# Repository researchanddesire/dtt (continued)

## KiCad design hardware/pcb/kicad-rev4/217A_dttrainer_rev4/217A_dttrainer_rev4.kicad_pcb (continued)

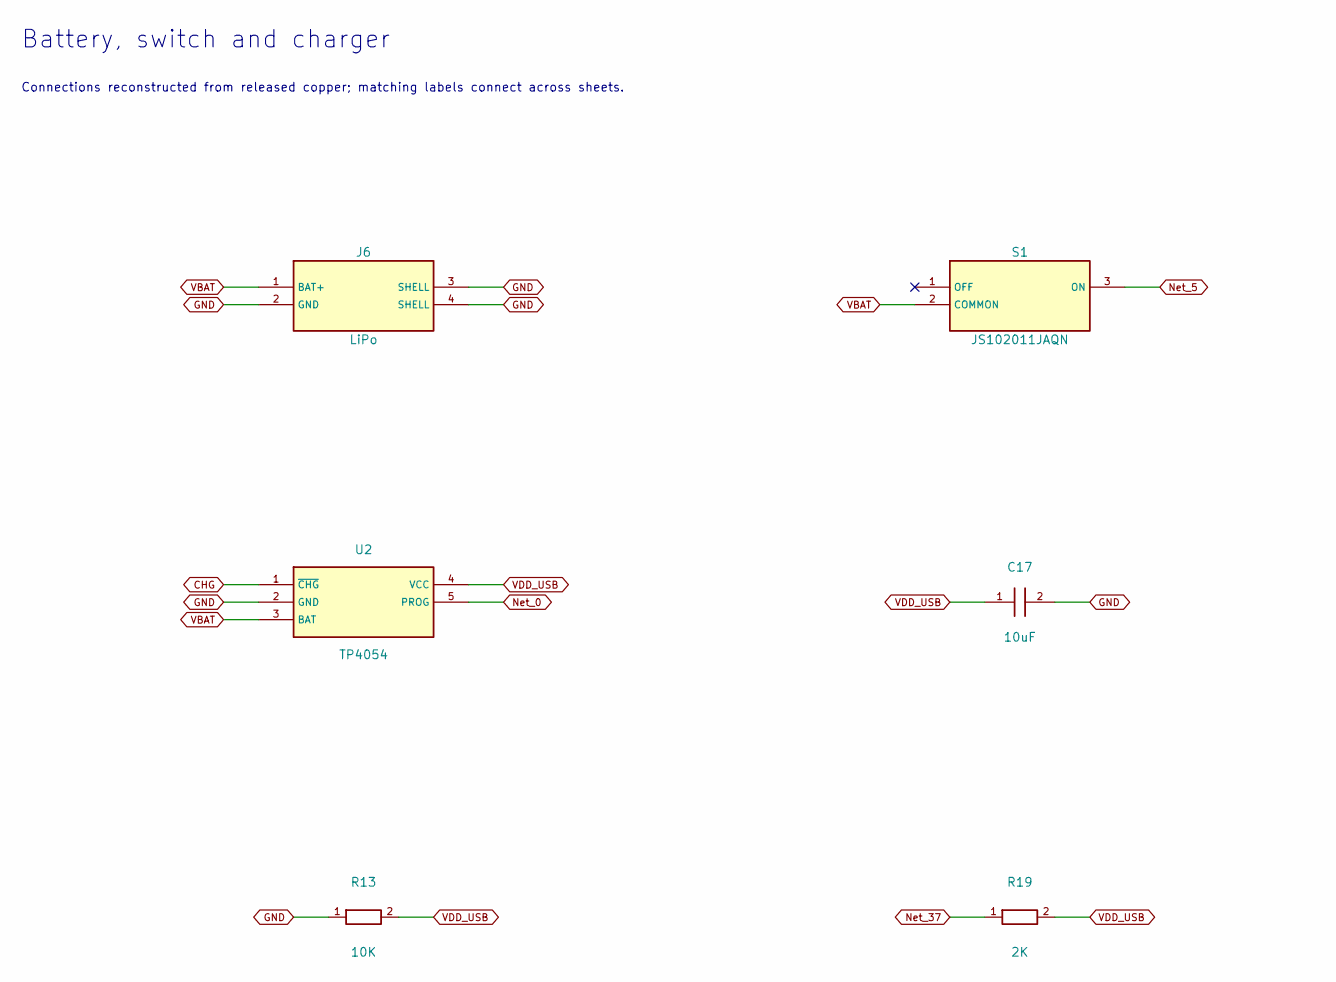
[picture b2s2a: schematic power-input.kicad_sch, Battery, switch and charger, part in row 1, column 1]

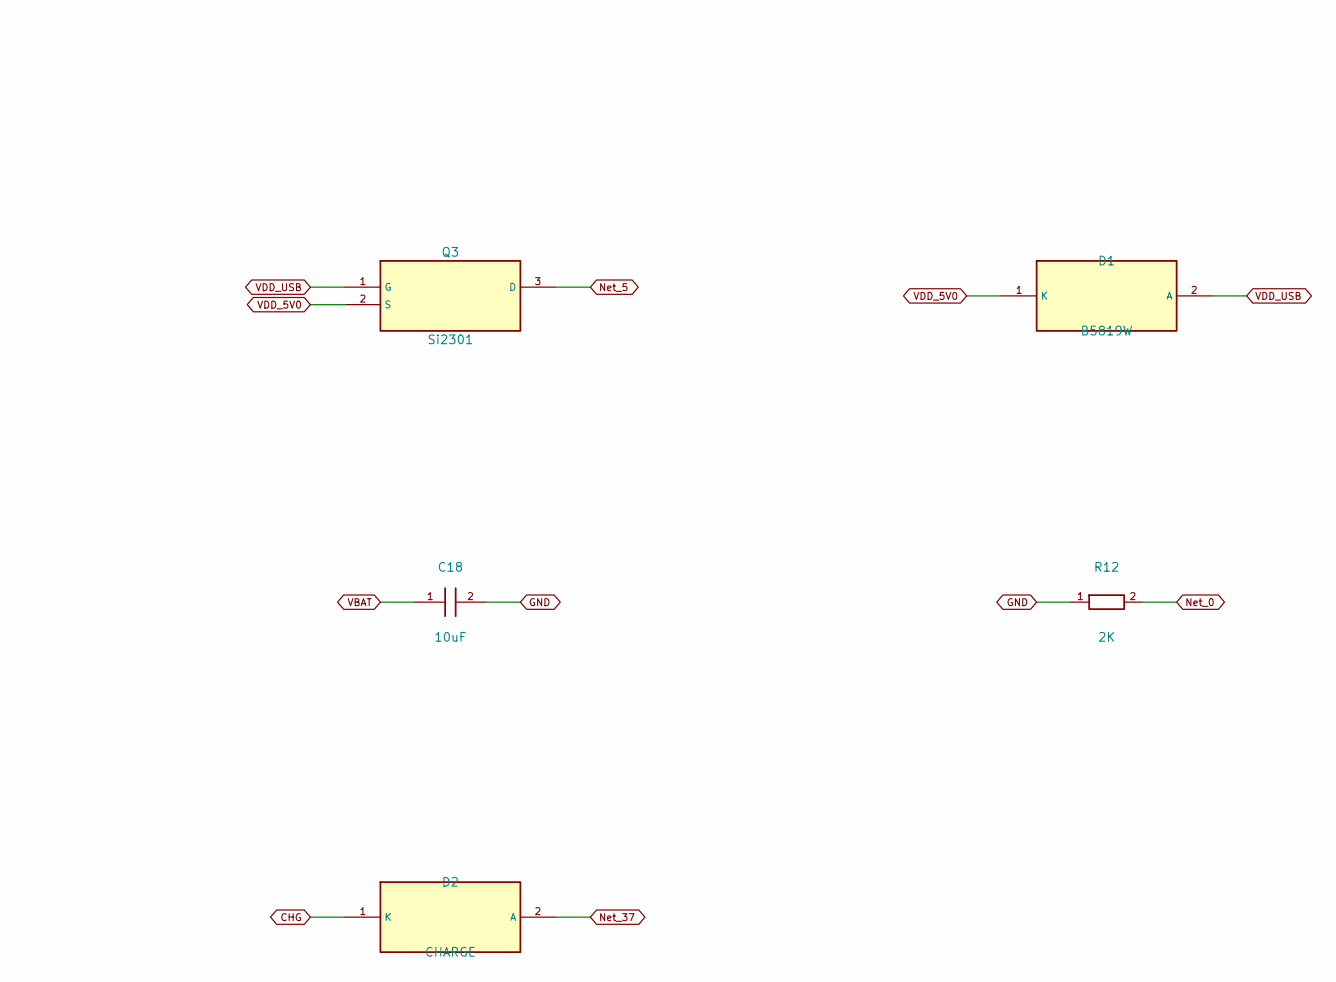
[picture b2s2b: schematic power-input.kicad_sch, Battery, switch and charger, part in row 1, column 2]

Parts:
C17: 10uF; C17; LCSC C89827
C18: 10uF; C18; LCSC C89827
D1: B5819W; D1; LCSC C22463588
D2: CHARGE; D2; LCSC C94868
J6: LiPo; J6; LCSC C2763702
Q3: Si2301; Q3; LCSC C727151
R12: 2K; R12; LCSC C105581
R13: 10K; R13; LCSC C99198
R19: 2K; R19; LCSC C105581
S1: JS102011JAQN; S1; LCSC C221658
U2: TP4054; U2; LCSC C32574

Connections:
CHG: D2.1 (K), U2.1 (~CHG); also elsewhere on the board
GND: C17.2, C18.2, J6.2 (GND), J6.3 (SHELL), J6.4 (SHELL), R12.1, R13.1, U2.2 (GND); also elsewhere on the board
Net_0: R12.2, U2.5 (PROG)
Net_5: Q3.3 (D), S1.3 (ON)
Net_37: D2.2 (A), R19.1
VBAT: C18.1, J6.1 (BAT+), S1.2 (COMMON), U2.3 (BAT); also elsewhere on the board
VDD_5V0: D1.1 (K), Q3.2 (S); also elsewhere on the board
VDD_USB: C17.1, D1.2 (A), Q3.1 (G), R13.2, R19.2, U2.4 (VCC); also elsewhere on the board

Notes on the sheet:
Battery, switch and charger
Connections reconstructed from released copper; matching labels connect across sheets.

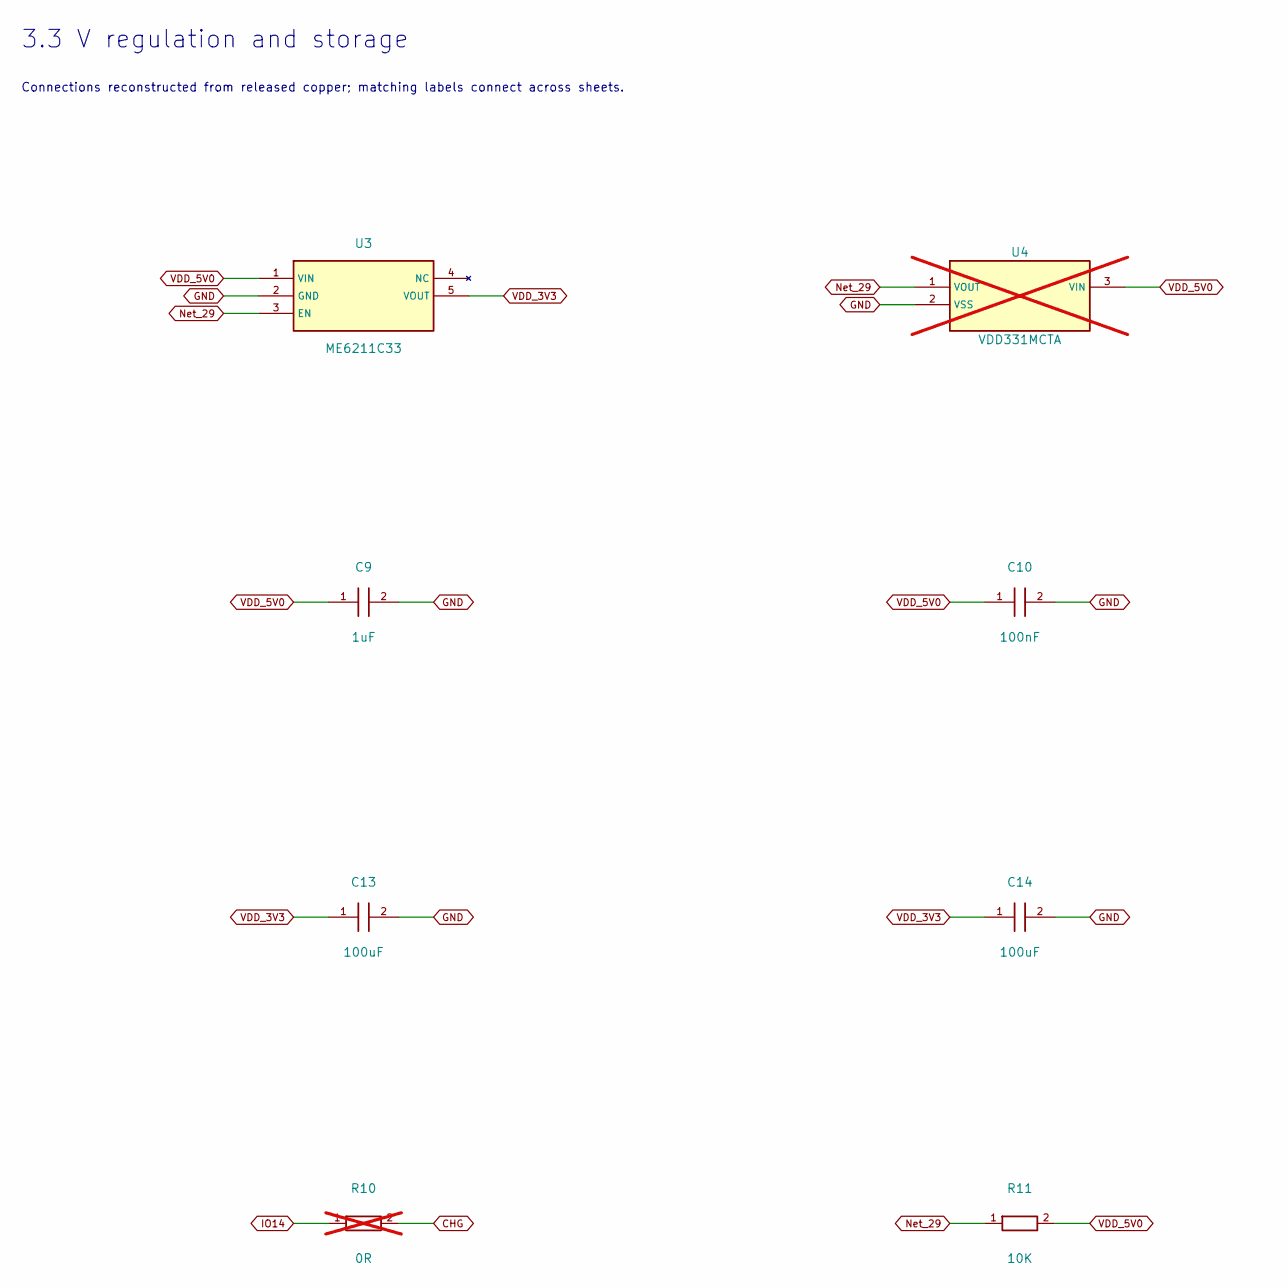
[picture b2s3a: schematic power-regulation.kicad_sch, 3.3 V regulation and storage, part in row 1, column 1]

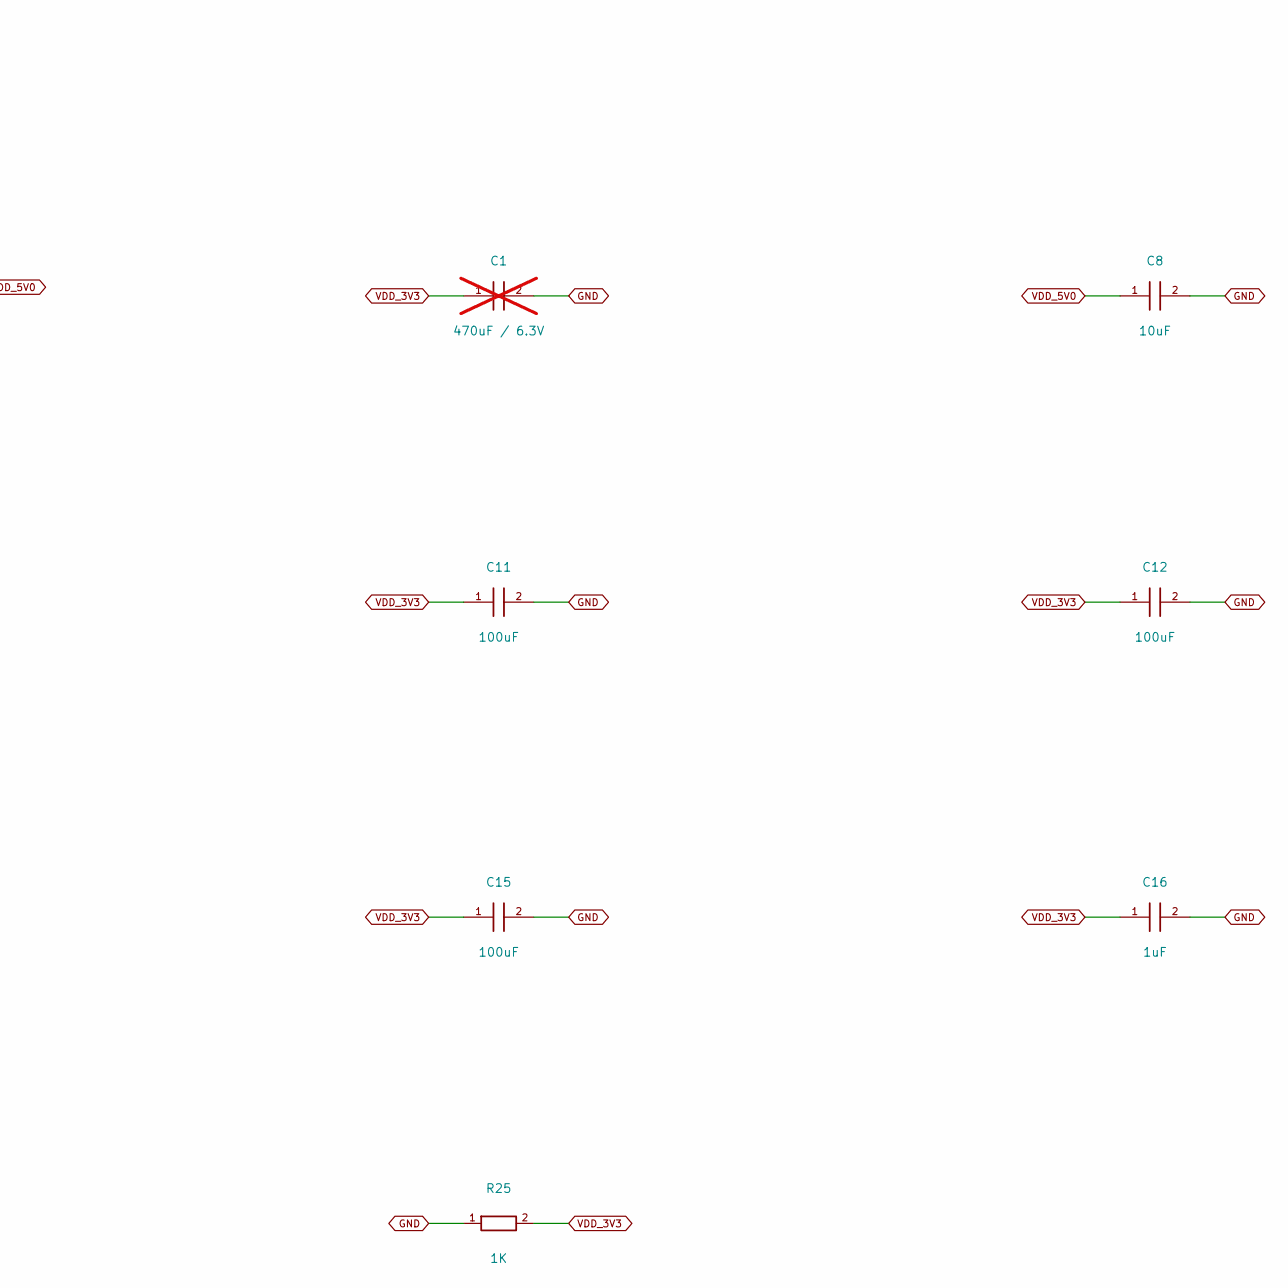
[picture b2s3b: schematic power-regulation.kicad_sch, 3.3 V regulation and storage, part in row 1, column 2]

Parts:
C1: 470uF / 6.3V; C1; LCSC DNP; not fitted
C8: 10uF; C8; LCSC C89827
C9: 1uF; C9; LCSC C106248
C10: 100nF; C10; LCSC C108079
C11: 100uF; C11; LCSC C15008
C12: 100uF; C12; LCSC C15008
C13: 100uF; C13; LCSC C15008
C14: 100uF; C14; LCSC C15008
C15: 100uF; C15; LCSC C15008
C16: 1uF; C16; LCSC C106248
R10: 0R; R10; LCSC DNP; not fitted
R11: 10K; R11; LCSC C99198
R25: 1K; R25; LCSC C14676
U3: ME6211C33; U3; LCSC C82942
U4: VDD331MCTA; U4; LCSC DNP; not fitted

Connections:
CHG: R10.2; also elsewhere on the board
GND: C1.2, C8.2, C9.2, C10.2, C11.2, C12.2, C13.2, C14.2, C15.2, C16.2, R25.1, U3.2 (GND), U4.2 (VSS); also elsewhere on the board
IO14: R10.1; also elsewhere on the board
Net_29: R11.1, U3.3 (EN), U4.1 (VOUT)
VDD_3V3: C1.1, C11.1, C12.1, C13.1, C14.1, C15.1, C16.1, R25.2, U3.5 (VOUT); also elsewhere on the board
VDD_5V0: C8.1, C9.1, C10.1, R11.2, U3.1 (VIN), U4.3 (VIN); also elsewhere on the board

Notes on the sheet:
3.3 V regulation and storage
Connections reconstructed from released copper; matching labels connect across sheets.

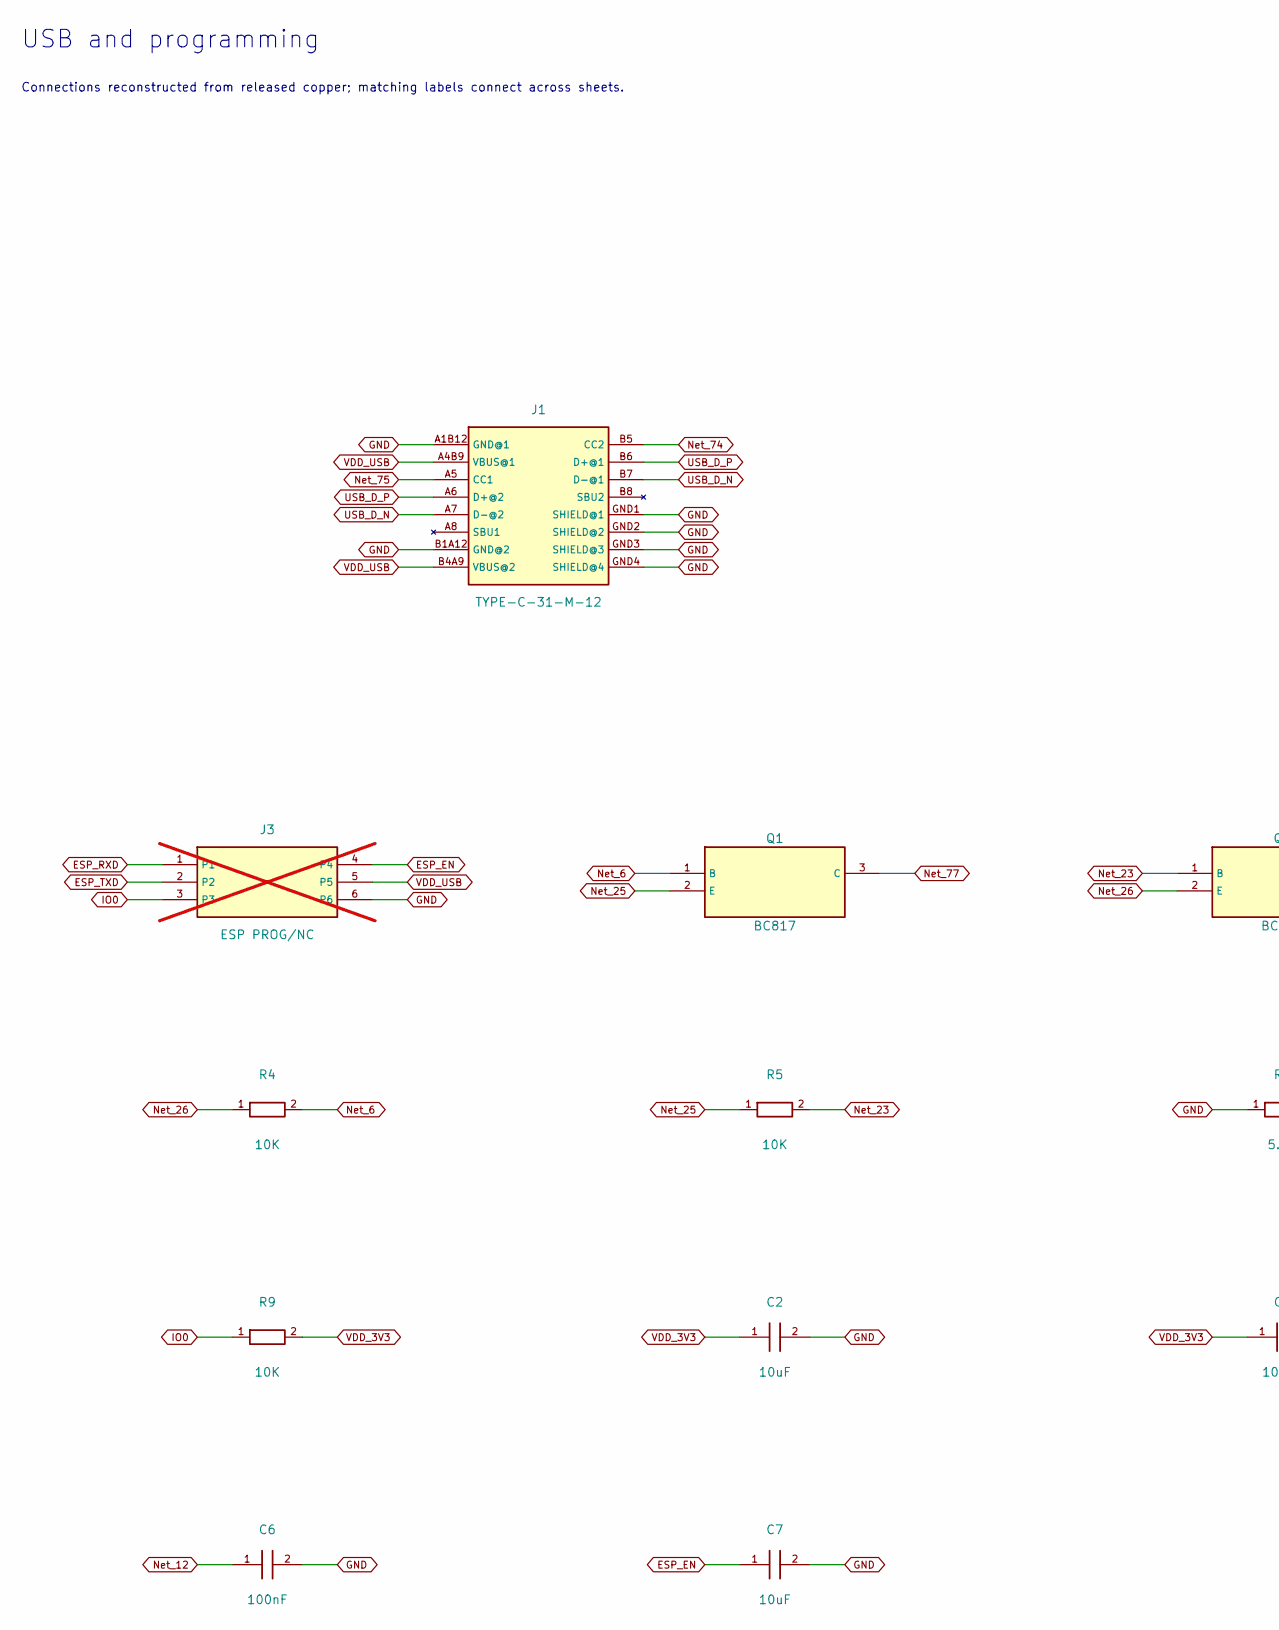
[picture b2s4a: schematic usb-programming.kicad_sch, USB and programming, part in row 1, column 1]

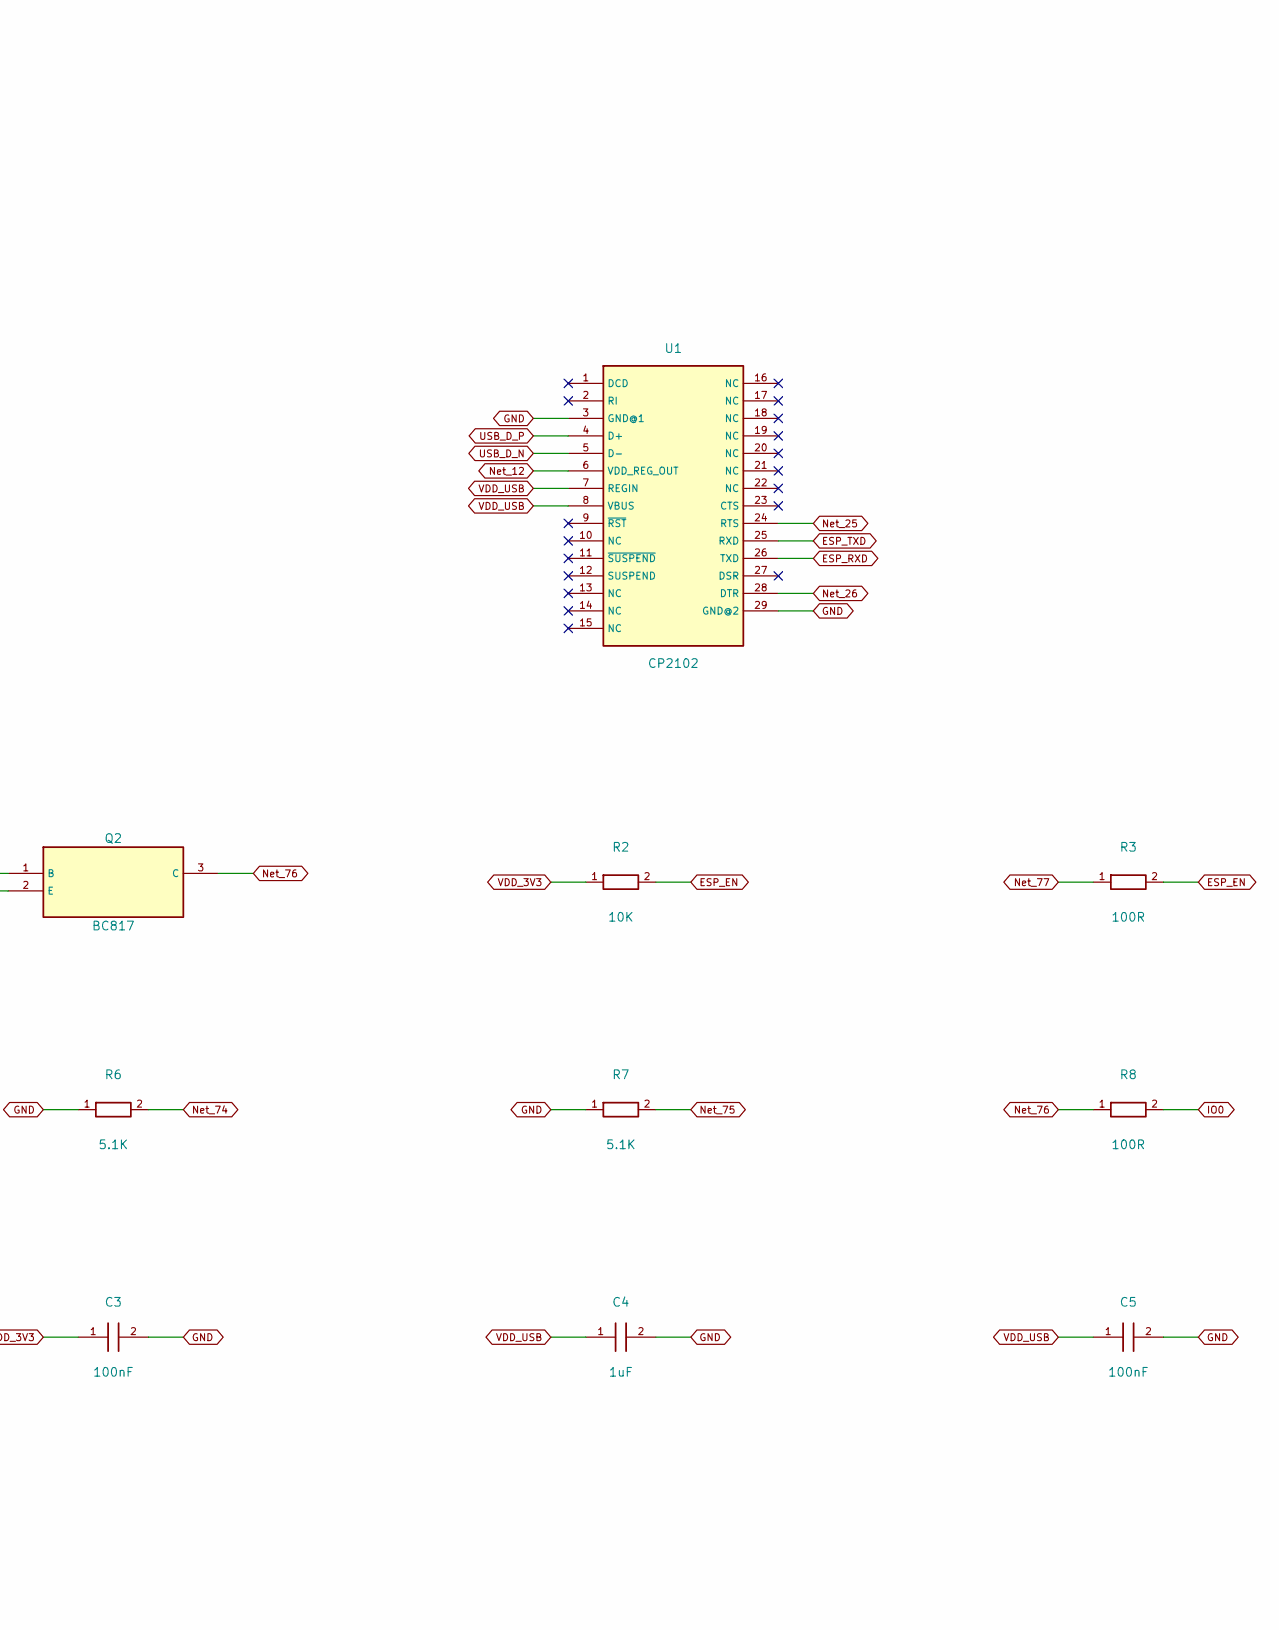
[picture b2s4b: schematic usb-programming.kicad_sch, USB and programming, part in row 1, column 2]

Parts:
C2: 10uF; C2; LCSC C237435
C3: 100nF; C3; LCSC C519438
C4: 1uF; C4; LCSC C106248
C5: 100nF; C5; LCSC C108079
C6: 100nF; C6; LCSC C108079
C7: 10uF; C7; LCSC C109457
J1: TYPE-C-31-M-12; J1; LCSC C165948
J3: ESP PROG/NC; J3; LCSC DNP; not fitted
Q1: BC817; Q1; LCSC C8658
Q2: BC817; Q2; LCSC C8658
R2: 10K; R2; LCSC C99198
R3: 100R; R3; LCSC C110091
R4: 10K; R4; LCSC C99198
R5: 10K; R5; LCSC C99198
R6: 5.1K; R6; LCSC C105580
R7: 5.1K; R7; LCSC C105580
R8: 100R; R8; LCSC C110091
R9: 10K; R9; LCSC C99198
U1: CP2102; U1; LCSC C6568

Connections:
ESP_EN: C7.1, J3.4, R2.2, R3.2; also elsewhere on the board
ESP_RXD: J3.1, U1.26 (TXD); also elsewhere on the board
ESP_TXD: J3.2, U1.25 (RXD); also elsewhere on the board
GND: C2.2, C3.2, C4.2, C5.2, C6.2, C7.2, J1.A1B12 (GND@1), J1.B1A12 (GND@2), J1.GND1 (SHIELD@1), J1.GND2 (SHIELD@2), J1.GND3 (SHIELD@3), J1.GND4 (SHIELD@4), J3.6, R6.1, R7.1, U1.3 (GND@1), U1.29 (GND@2); also elsewhere on the board
IO0: J3.3, R8.2, R9.1; also elsewhere on the board
Net_6: Q1.1 (B), R4.2
Net_12: C6.1, U1.6 (VDD_REG_OUT)
Net_23: Q2.1 (B), R5.2
Net_25: Q1.2 (E), R5.1, U1.24 (RTS)
Net_26: Q2.2 (E), R4.1, U1.28 (DTR)
Net_74: J1.B5 (CC2), R6.2
Net_75: J1.A5 (CC1), R7.2
Net_76: Q2.3 (C), R8.1
Net_77: Q1.3 (C), R3.1
USB_D_N: J1.A7 (D-@2), J1.B7 (D-@1), U1.5 (D-)
USB_D_P: J1.A6 (D+@2), J1.B6 (D+@1), U1.4 (D+)
VDD_3V3: C2.1, C3.1, R2.1, R9.2; also elsewhere on the board
VDD_USB: C4.1, C5.1, J1.A4B9 (VBUS@1), J1.B4A9 (VBUS@2), J3.5, U1.7 (REGIN), U1.8 (VBUS); also elsewhere on the board

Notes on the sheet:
USB and programming
Connections reconstructed from released copper; matching labels connect across sheets.

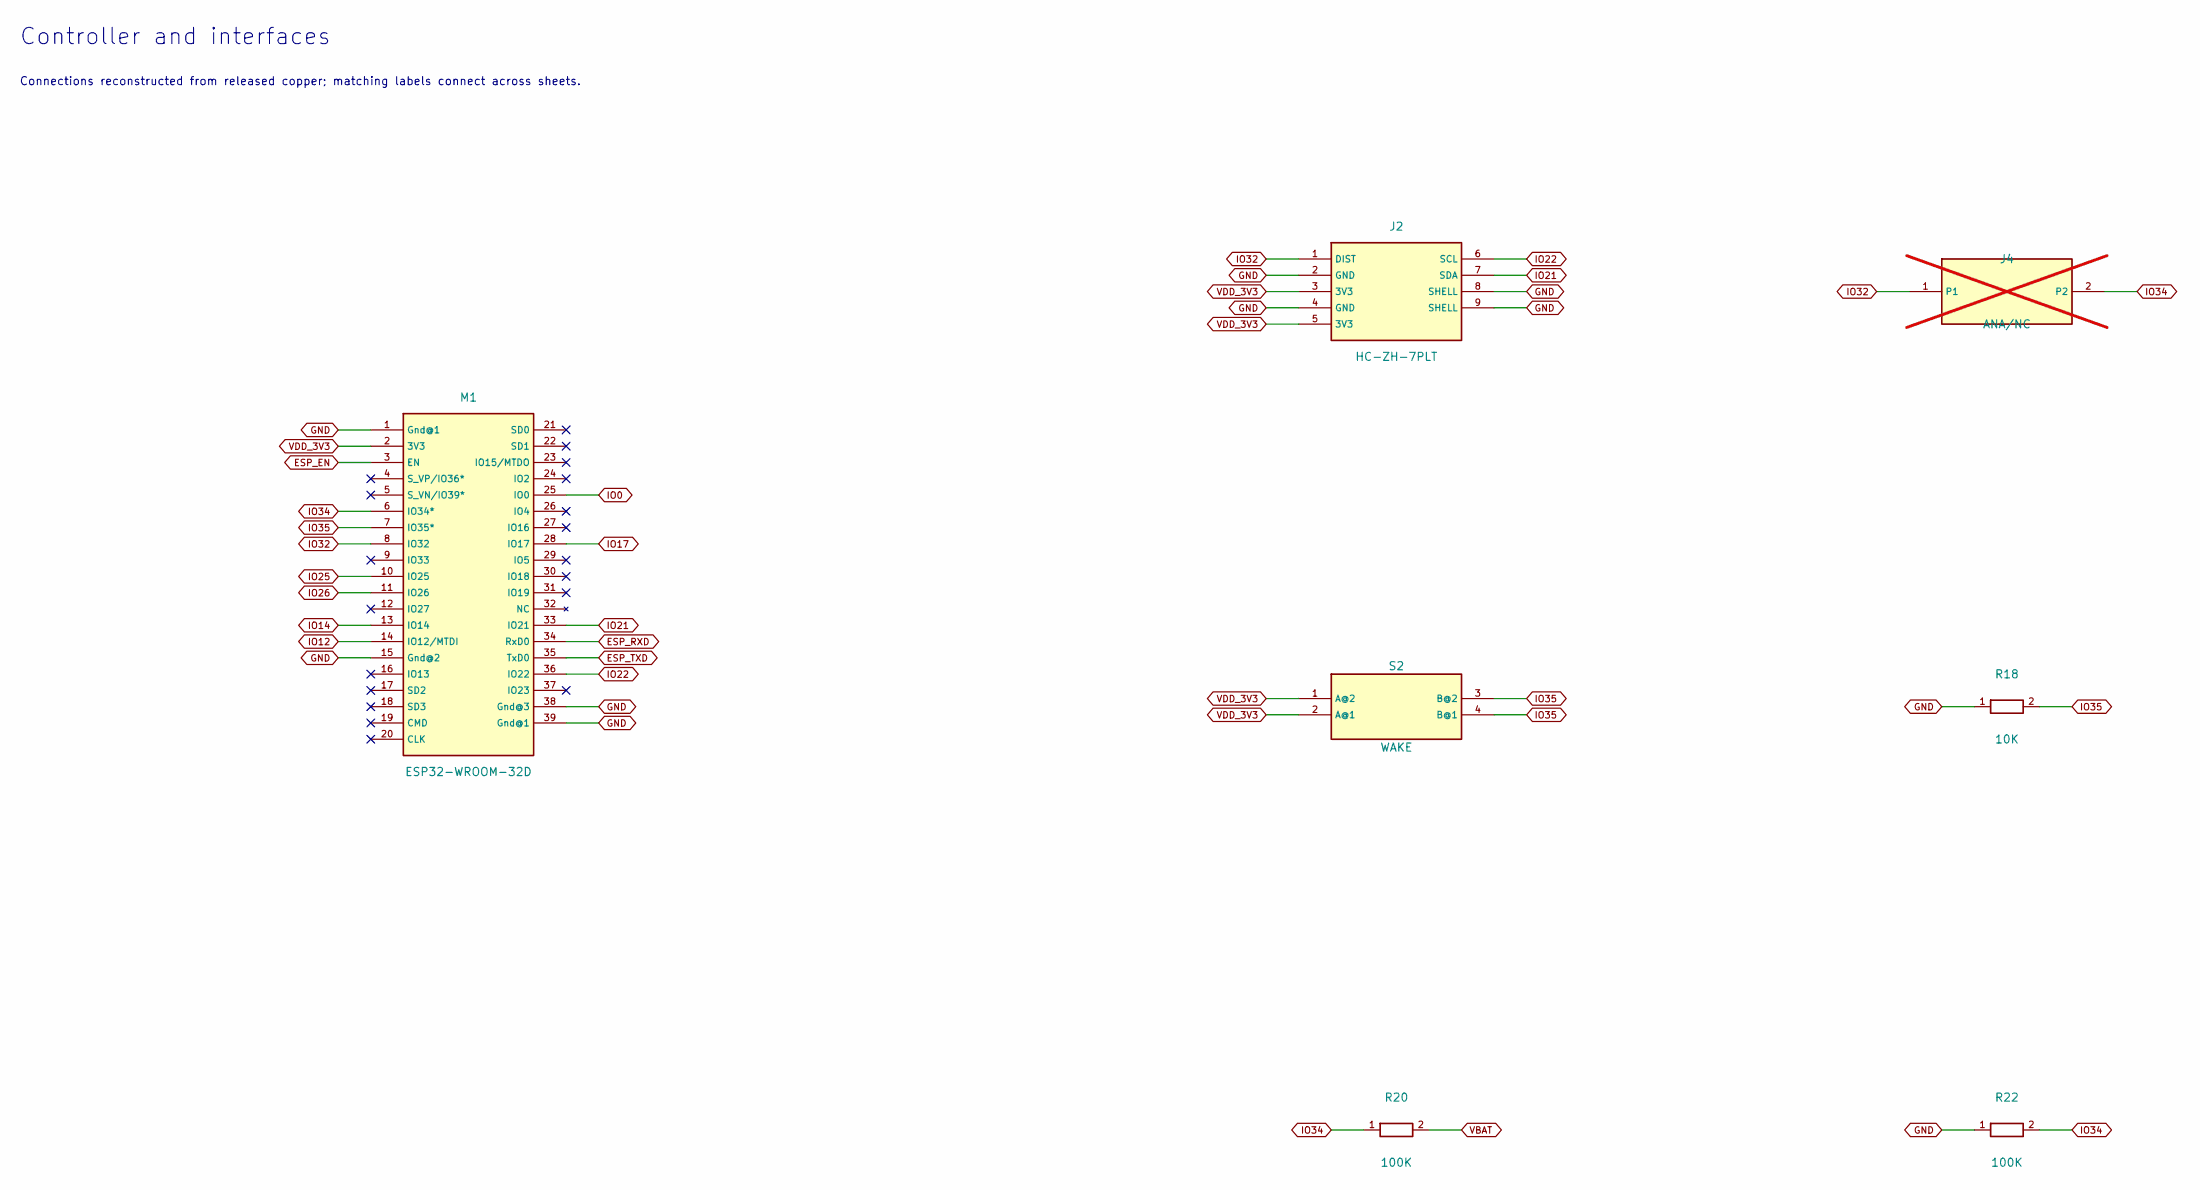
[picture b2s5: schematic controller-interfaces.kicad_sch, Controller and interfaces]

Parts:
J2: HC-ZH-7PLT; J2; LCSC HC-ZH-7PLT
J4: ANA/NC; J4; LCSC DNP; not fitted
M1: ESP32-WROOM-32D; M1; LCSC C701343
R18: 10K; R18; LCSC C99198
R20: 100K; R20; LCSC C14675
R22: 100K; R22; LCSC C14675
S2: WAKE; S2; LCSC C381038

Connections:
ESP_EN: M1.3 (EN); also elsewhere on the board
ESP_RXD: M1.34 (RxD0); also elsewhere on the board
ESP_TXD: M1.35 (TxD0); also elsewhere on the board
GND: J2.2 (GND), J2.4 (GND), J2.8 (SHELL), J2.9 (SHELL), M1.1 (Gnd@1), M1.15 (Gnd@2), M1.38 (Gnd@3), M1.39 (Gnd@1), R18.1, R22.1; also elsewhere on the board
IO0: M1.25 (IO0); also elsewhere on the board
IO12: M1.14 (IO12/MTDI); also elsewhere on the board
IO14: M1.13 (IO14); also elsewhere on the board
IO17: M1.28 (IO17); also elsewhere on the board
IO21: J2.7 (SDA), M1.33 (IO21)
IO22: J2.6 (SCL), M1.36 (IO22)
IO25: M1.10 (IO25); also elsewhere on the board
IO26: M1.11 (IO26); also elsewhere on the board
IO32: J2.1 (DIST), J4.1, M1.8 (IO32)
IO34: J4.2, M1.6 (IO34*), R20.1, R22.2
IO35: M1.7 (IO35*), R18.2, S2.3 (B@2), S2.4 (B@1)
VBAT: R20.2; also elsewhere on the board
VDD_3V3: J2.3 (3V3), J2.5 (3V3), M1.2 (3V3), S2.1 (A@2), S2.2 (A@1); also elsewhere on the board

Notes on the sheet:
Controller and interfaces
Connections reconstructed from released copper; matching labels connect across sheets.

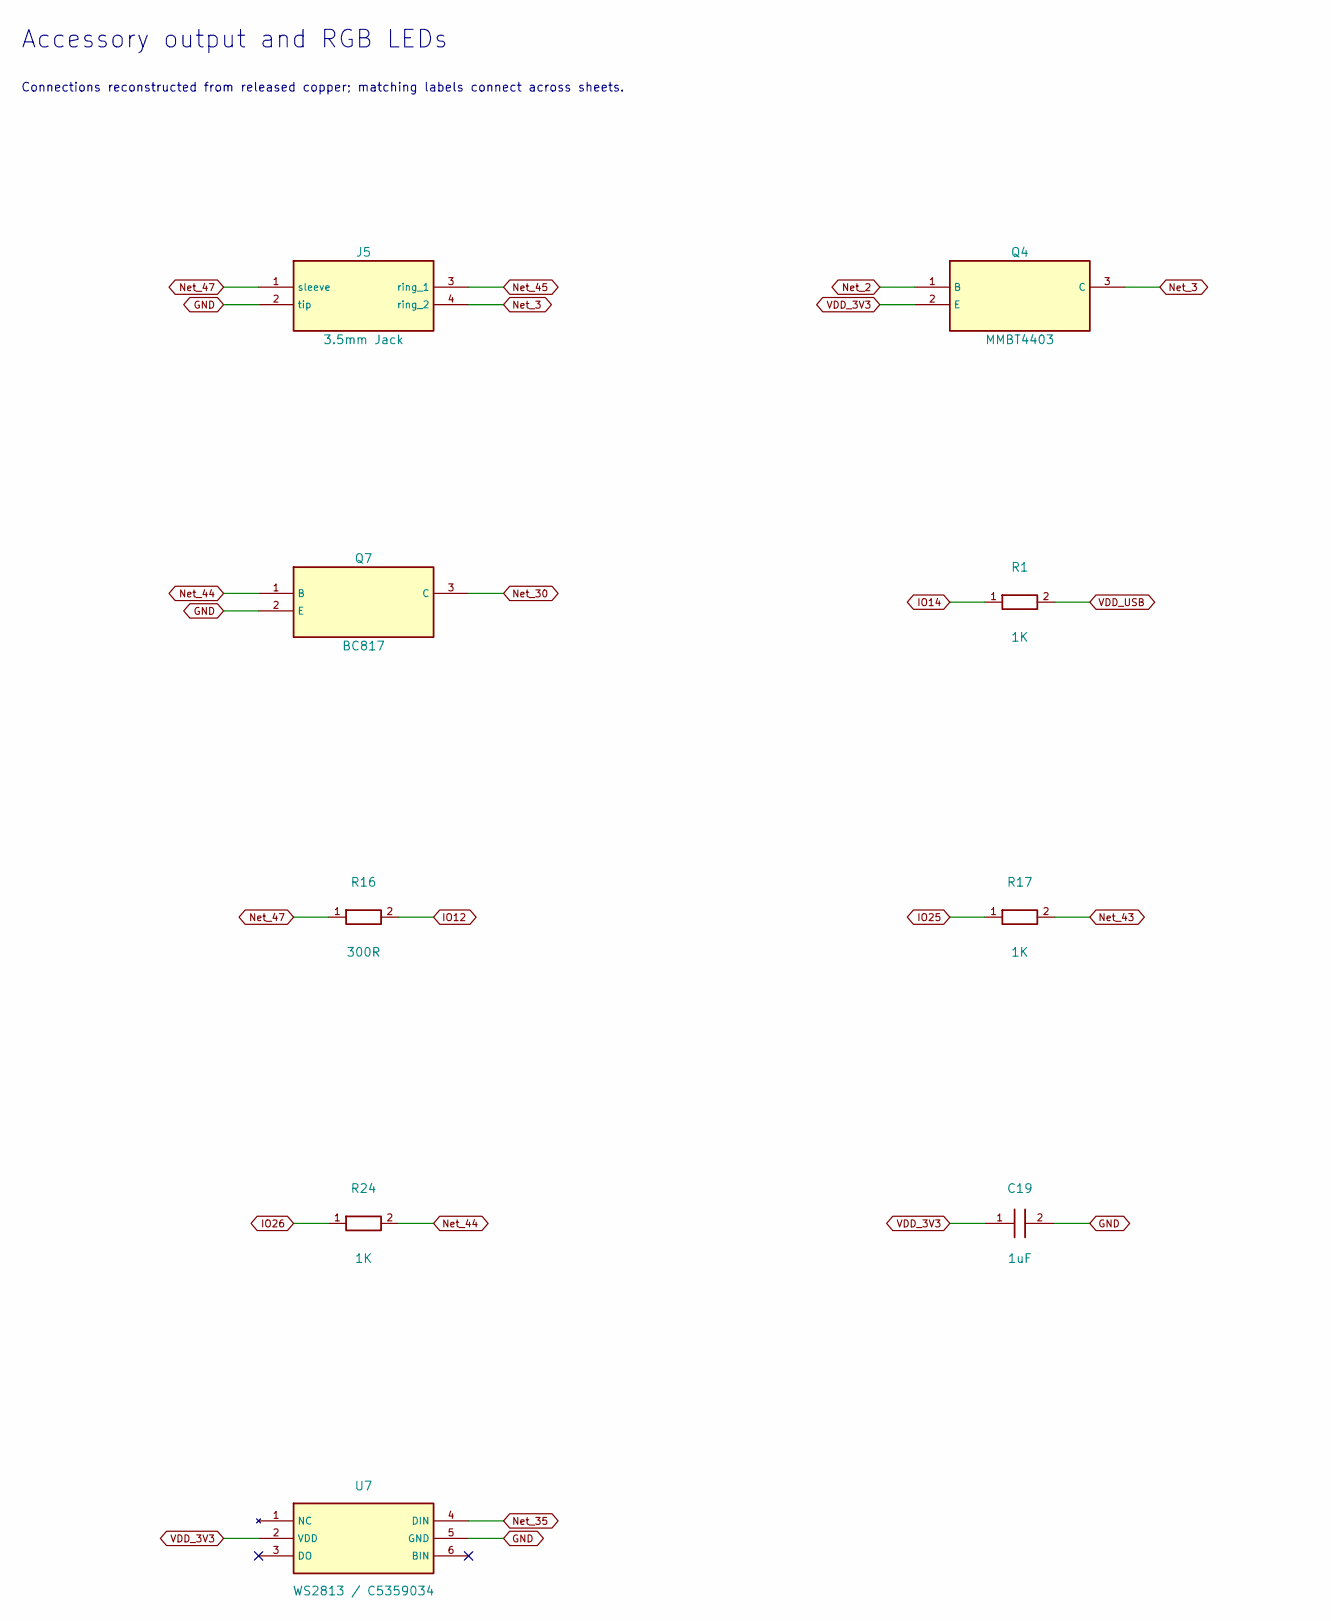
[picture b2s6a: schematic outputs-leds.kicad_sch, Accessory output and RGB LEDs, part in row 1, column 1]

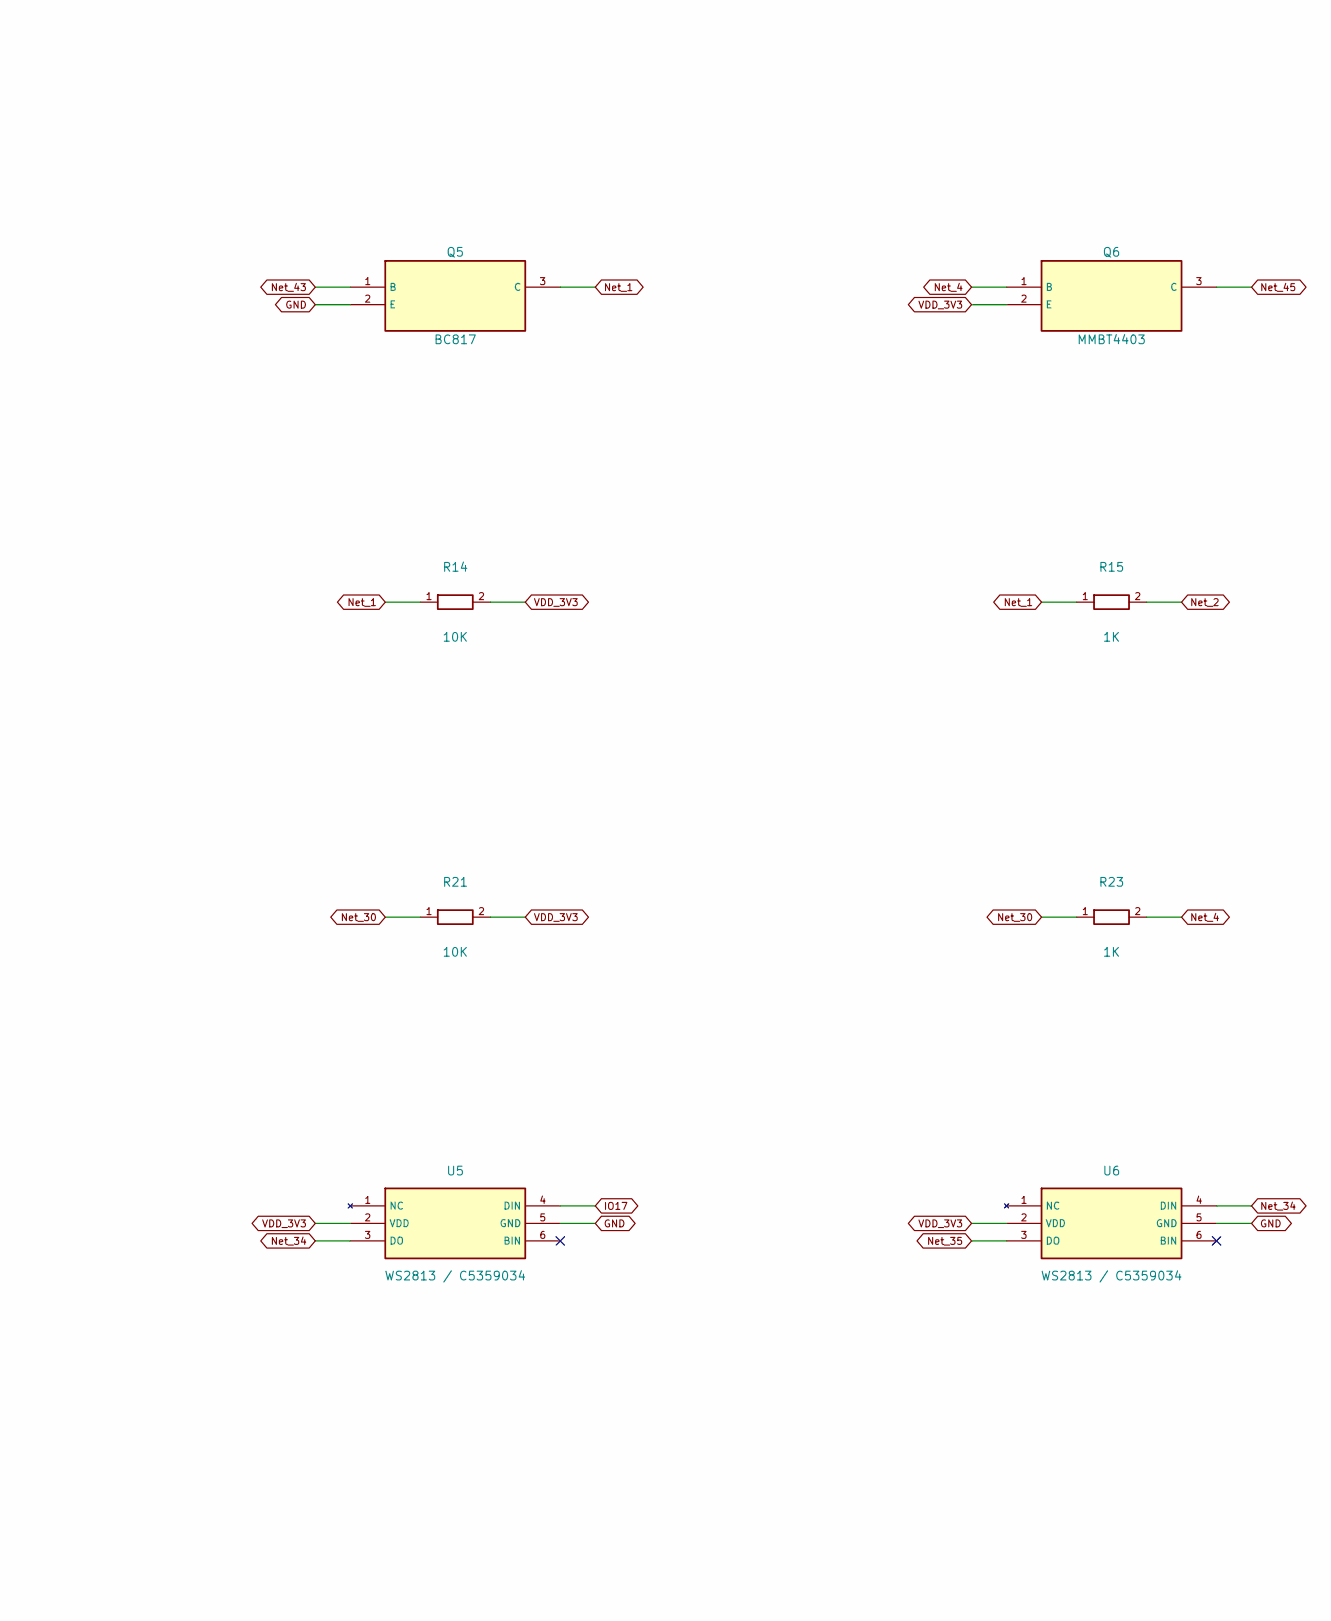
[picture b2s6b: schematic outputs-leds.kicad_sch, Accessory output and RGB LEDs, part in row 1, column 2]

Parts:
C19: 1uF; C19; LCSC C106248
J5: 3.5mm Jack; J5; LCSC C431535
Q4: MMBT4403; Q4; LCSC C78864
Q5: BC817; Q5; LCSC C8658
Q6: MMBT4403; Q6; LCSC C78864
Q7: BC817; Q7; LCSC C8658
R1: 1K; R1; LCSC C14676
R14: 10K; R14; LCSC C99198
R15: 1K; R15; LCSC C14676
R16: 300R; R16; LCSC C137637
R17: 1K; R17; LCSC C14676
R21: 10K; R21; LCSC C99198
R23: 1K; R23; LCSC C14676
R24: 1K; R24; LCSC C14676
U5: WS2813 / C5359034; U5; LCSC C5359034
U6: WS2813 / C5359034; U6; LCSC C5359034
U7: WS2813 / C5359034; U7; LCSC C5359034

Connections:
GND: C19.2, J5.2 (tip), Q5.2 (E), Q7.2 (E), U5.5 (GND), U6.5 (GND), U7.5 (GND); also elsewhere on the board
IO12: R16.2; also elsewhere on the board
IO14: R1.1; also elsewhere on the board
IO17: U5.4 (DIN); also elsewhere on the board
IO25: R17.1; also elsewhere on the board
IO26: R24.1; also elsewhere on the board
Net_1: Q5.3 (C), R14.1, R15.1
Net_2: Q4.1 (B), R15.2
Net_3: J5.4 (ring_2), Q4.3 (C)
Net_4: Q6.1 (B), R23.2
Net_30: Q7.3 (C), R21.1, R23.1
Net_34: U5.3 (DO), U6.4 (DIN)
Net_35: U6.3 (DO), U7.4 (DIN)
Net_43: Q5.1 (B), R17.2
Net_44: Q7.1 (B), R24.2
Net_45: J5.3 (ring_1), Q6.3 (C)
Net_47: J5.1 (sleeve), R16.1
VDD_3V3: C19.1, Q4.2 (E), Q6.2 (E), R14.2, R21.2, U5.2 (VDD), U6.2 (VDD), U7.2 (VDD); also elsewhere on the board
VDD_USB: R1.2; also elsewhere on the board

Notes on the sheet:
Accessory output and RGB LEDs
Connections reconstructed from released copper; matching labels connect across sheets.
